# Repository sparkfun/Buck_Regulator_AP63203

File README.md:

SparkFun Buck Regulator and Baby Buck Regulator
========================================

<table class="table table-hover table-striped table-bordered">
    <tr>
        <th class="text-center"> 
        </th>
        <th class="text-center">
        </th>
    </tr>
    <tr align="center">
        <td></td>
        <td></td>
    </tr>
    <tr align="center">
        <td><a href="https://www.sparkfun.com/products/18356">SparkFun Buck Regulator Breakout - 3.3V (AP63203)</a></td>
        <td><a href="https://www.sparkfun.com/products/18357">BabyBuck Regulator Breakout - 3.3V (AP63203)</a></td>
    </tr>
</table>

Who doesn't occasionally need power regulation? We certainly do, so we've designed the SparkFun Buck Regulator and Baby Buck Regulator Breakouts to help us with just such a task. Featuring the AP63203 from Diodes Inc, these breakout boards take advantage of a 2A synchronous buck converter that has a wide input voltage range of 3.8V to 32V and fully integrated 125mΩ high-side power MOSFET/68mΩ lowside power MOSFET to provide high-efficiency step-down DC/DC conversion. All of this snuggled up in a low-profile, TSOT26 package that's integrated into either a 1in. by 1in. or 0.4x0.5" board. 

Input power for the Buck Regulator can be supplied in a number of ways. There are screw terminals on the right side of the board, solder pads for a barrel jack, which can be mounted on the top or bottom side of the board, and the plated through holes on the left side of the board can all be used as input. Output can be obtained via the screw terminals or the plated through holes. Additionally, to dissipate some of the excess heat, we've added a copper pad for a heat sink on the back of the board.

Unlike it's sibling, the BabyBuck sacrifices power option flexibility for space. Don't worry, though, because you can still use the plated through holes for input and output power. With some simple [right-angle headers](https://www.sparkfun.com/products/553), you'll be up and running in no time.

Frequency Spread Spectrum (FSS) reduces EMI and a proprietary gate driver scheme resists switching node ringing without sacrificing MOSFET turn-on and turn-off times, which further erases high-frequency radiated EMI noise.

Repository Contents
-------------------

* **/SparkFun Buck Regulator - AP63203**
    * **/Hardware** - Eagle design files (.brd, .sch)
        * **/Production** - Production panel files (.brd)
* **/SparkFun BabyBuck Regulator - AP63203**
    * **/Hardware** - Eagle design files (.brd, .sch)
        * **/Production** - Production panel files (.brd)

Documentation
--------------
* **[Hookup Guide](https://learn.sparkfun.com/tutorials/buck-regulator-hookup-guide)** - Basic hookup guide for the Buck Regulator and Baby Buck Regulator.
* **[SparkFun Fritzing repo](https://github.com/sparkfun/Fritzing_Parts)** - Fritzing diagrams for SparkFun products.

License Information
-------------------

This product is _**open source**_! 

Please review the LICENSE.md file for license information. 

If you have any questions or concerns on licensing, please contact technical support on our [SparkFun forums](https://forum.sparkfun.com/viewforum.php?f=152).

Distributed as-is; no warranty is given.

- Your friends at SparkFun.

_<COLLABORATION CREDIT>_

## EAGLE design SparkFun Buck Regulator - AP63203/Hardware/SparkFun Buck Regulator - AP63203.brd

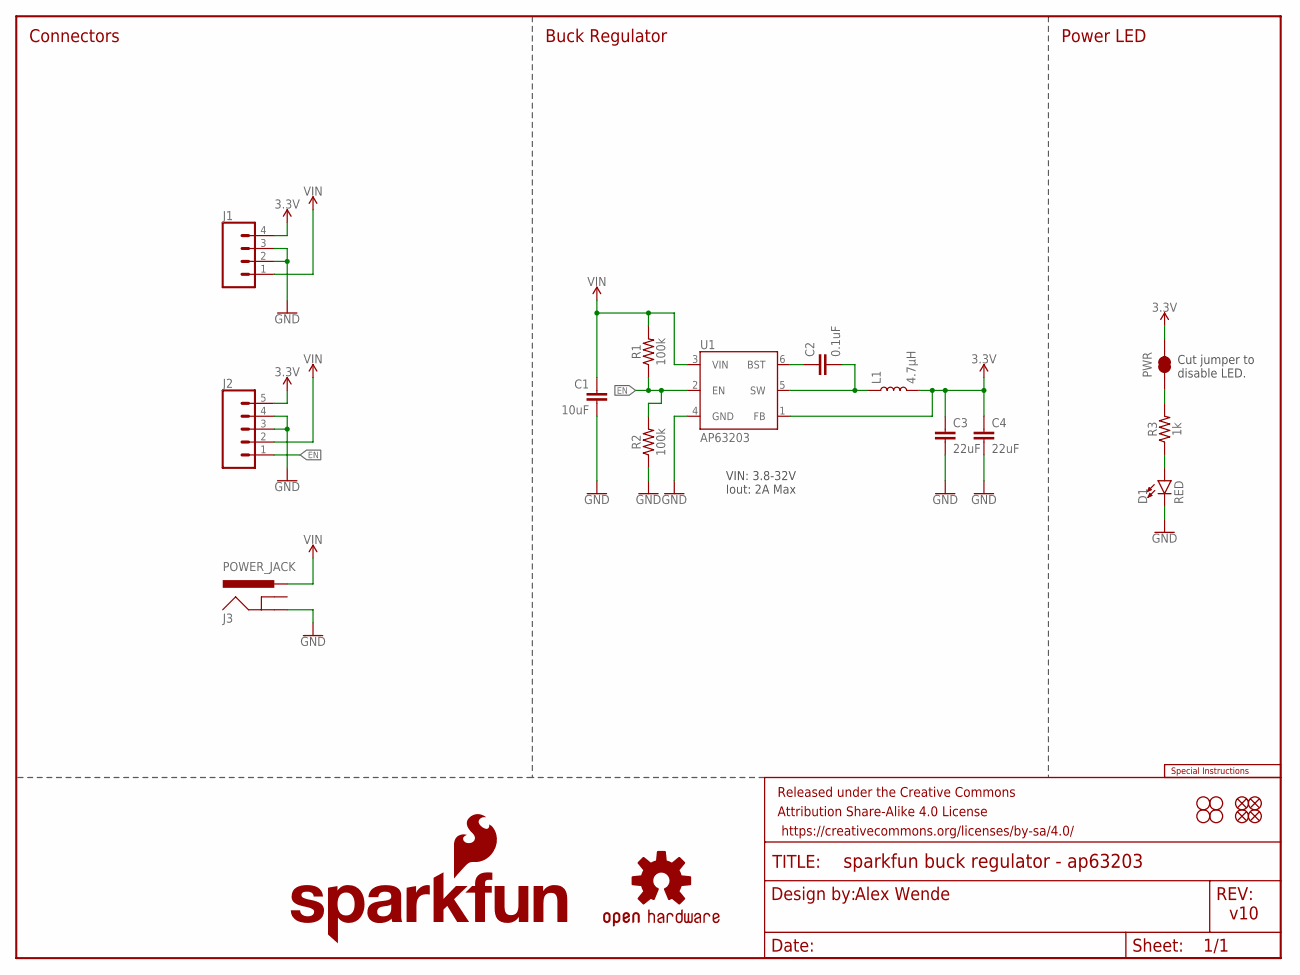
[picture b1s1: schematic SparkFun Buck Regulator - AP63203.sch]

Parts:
C1: 10uF; 1210
C2: 0.1uF; 0603
C3, C4: 22uF; 0603
D1: RED; LED-0603
FD1, FD2, FD3, FD4: FIDUCIALUFIDUCIAL; FIDUCIAL-MICRO
FRAME1: FRAME-LETTER; CREATIVE_COMMONS
H1, H2, H3, H4: STAND-OFF
J1: CONN_04SCREW; SCREWTERMINAL-3.5MM-4
J2: CONN_05NO_SILK; 1X05_NO_SILK
J3: POWER_JACK; POWER_JACK_PTH_SLOT
L1: 4.7μH; INDUCTOR_4X4MM
LOGO1: SFE_LOGO_NAME_FLAME.1_INCH; SFE_LOGO_NAME_FLAME_.1
LOGO2: OSHW-LOGOS; OSHW-LOGO-S
LOGO3: SPECIAL_INSTRUCTIONS-ORDERING; ORDERING_INSTRUCTIONS
PWR: JUMPER-SMT_2_NC_TRACE_SILK; SMT-JUMPER_2_NC_TRACE_SILK
R1, R2: 100k; 0603
R3: 1k; 0603
U1: AP63203; SOT23-6

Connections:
3.3V: C3.1, C4.1, J1.4, J2.5, L1.P$2 (2), PWR.2, U1.1 (FB)
EN: J2.1, R1.1, R2.2, U1.2 (EN)
GND: C1.2, C3.2, C4.2, D1.C, J1.2, J1.3, J2.3, J2.4, J3.GND, R2.1, U1.4 (GND)
unnamed: D1.A, R3.1
unnamed: PWR.1, R3.2
unnamed: C2.1, U1.6 (BST)
unnamed: C2.2, L1.P$1 (1), U1.5 (SW)
VIN: C1.1, J1.1, J2.2, J3.PWR, R1.2, U1.3 (VIN)

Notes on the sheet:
Alex Wende
v10
Buck Regulator
Connectors
VIN: 3.8-32V Iout: 2A Max
Power LED
Cut jumper to disable LED.

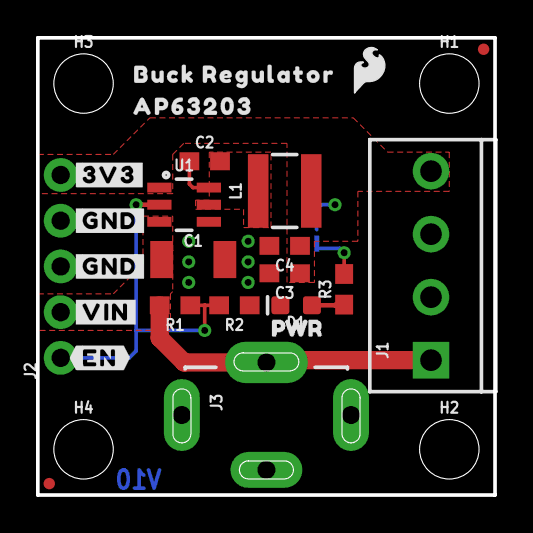
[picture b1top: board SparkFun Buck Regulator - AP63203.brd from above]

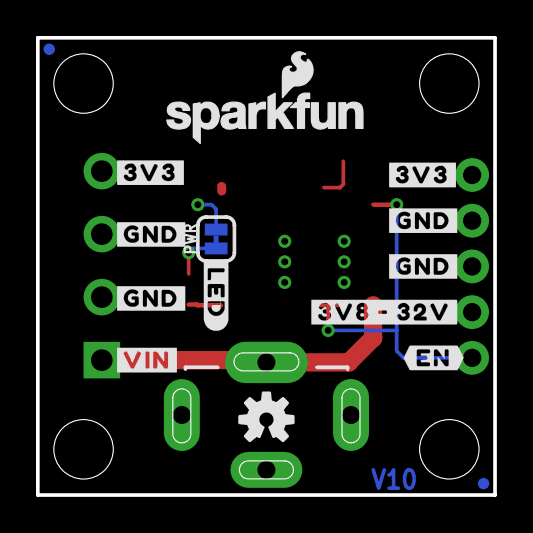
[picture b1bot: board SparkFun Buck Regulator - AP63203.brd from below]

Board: 2 copper layers, 25.4 x 25.4 mm, 45 parts (15 on the bottom side), 8 nets.

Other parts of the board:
U$1, U$2, U$13: #3V3#0
U$3, U$4, U$5, U$10, U$11, U$12: #GND#0
U$6, U$8: #VIN#0
U$7, U$14: #EN#0
U$9: #3V8_#_32V#0
U$15: BUCK_REGULATOR0
U$16: #LED#0
U$17: SFE_LOGO_FLAME_.1
U$18: PWR1
U$20: AP632030

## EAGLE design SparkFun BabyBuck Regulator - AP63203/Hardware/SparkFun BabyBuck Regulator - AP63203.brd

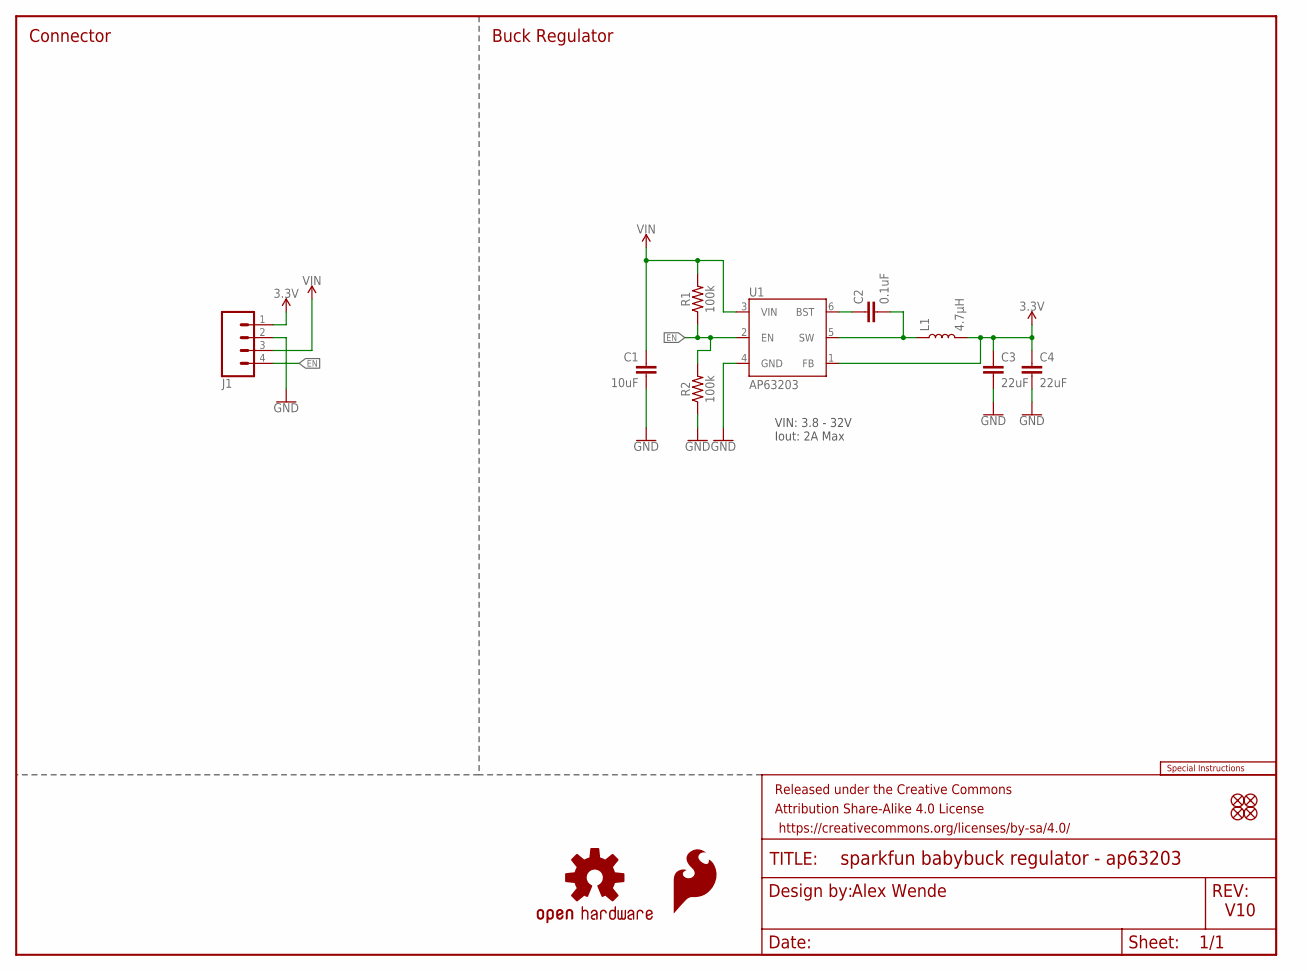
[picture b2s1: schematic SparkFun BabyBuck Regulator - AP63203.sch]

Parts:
C1: 10uF; 1210
C2: 0.1uF; 0603
C3, C4: 22uF; 0603
FD1, FD2, FD3, FD4: FIDUCIAL0.2MM; FIDUCIAL-0.2MM
FRAME1: FRAME-LETTER; CREATIVE_COMMONS
J1: CONN_041X04_NO_SILK; 1X04_NO_SILK
L1: 4.7μH; INDUCTOR_4X4MM
LOGO1: SFE_LOGO_FLAME.1_INCH; SFE_LOGO_FLAME_.1
LOGO2: OSHW-LOGOS; OSHW-LOGO-S
LOGO3: SPECIAL_INSTRUCTIONS-ORDERING; ORDERING_INSTRUCTIONS
R1, R2: 100k; 0603
U1: AP63203; SOT23-6

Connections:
3.3V: C3.1, C4.1, J1.1, L1.P$2 (2), U1.1 (FB)
EN: J1.4, R1.1, R2.2, U1.2 (EN)
GND: C1.2, C3.2, C4.2, J1.2, R2.1, U1.4 (GND)
unnamed: C2.1, U1.6 (BST)
unnamed: C2.2, L1.P$1 (1), U1.5 (SW)
VIN: C1.1, J1.3, R1.2, U1.3 (VIN)

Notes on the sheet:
Alex Wende
V10
Buck Regulator
Connector
VIN: 3.8 - 32V Iout: 2A Max

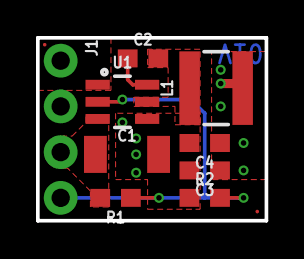
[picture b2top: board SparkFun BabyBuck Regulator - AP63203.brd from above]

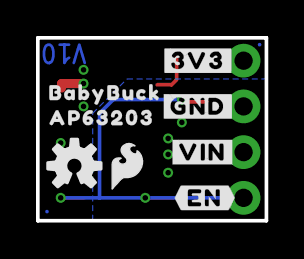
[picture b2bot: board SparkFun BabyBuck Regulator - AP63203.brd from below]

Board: 2 copper layers, 12.7 x 10.2 mm, 23 parts (10 on the bottom side), 6 nets.

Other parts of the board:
U$1: #3V3#0
U$2: #GND#0
U$3: #VIN#0
U$4: #EN#0
U$7: AP632030
U$8: BABYBUCK0

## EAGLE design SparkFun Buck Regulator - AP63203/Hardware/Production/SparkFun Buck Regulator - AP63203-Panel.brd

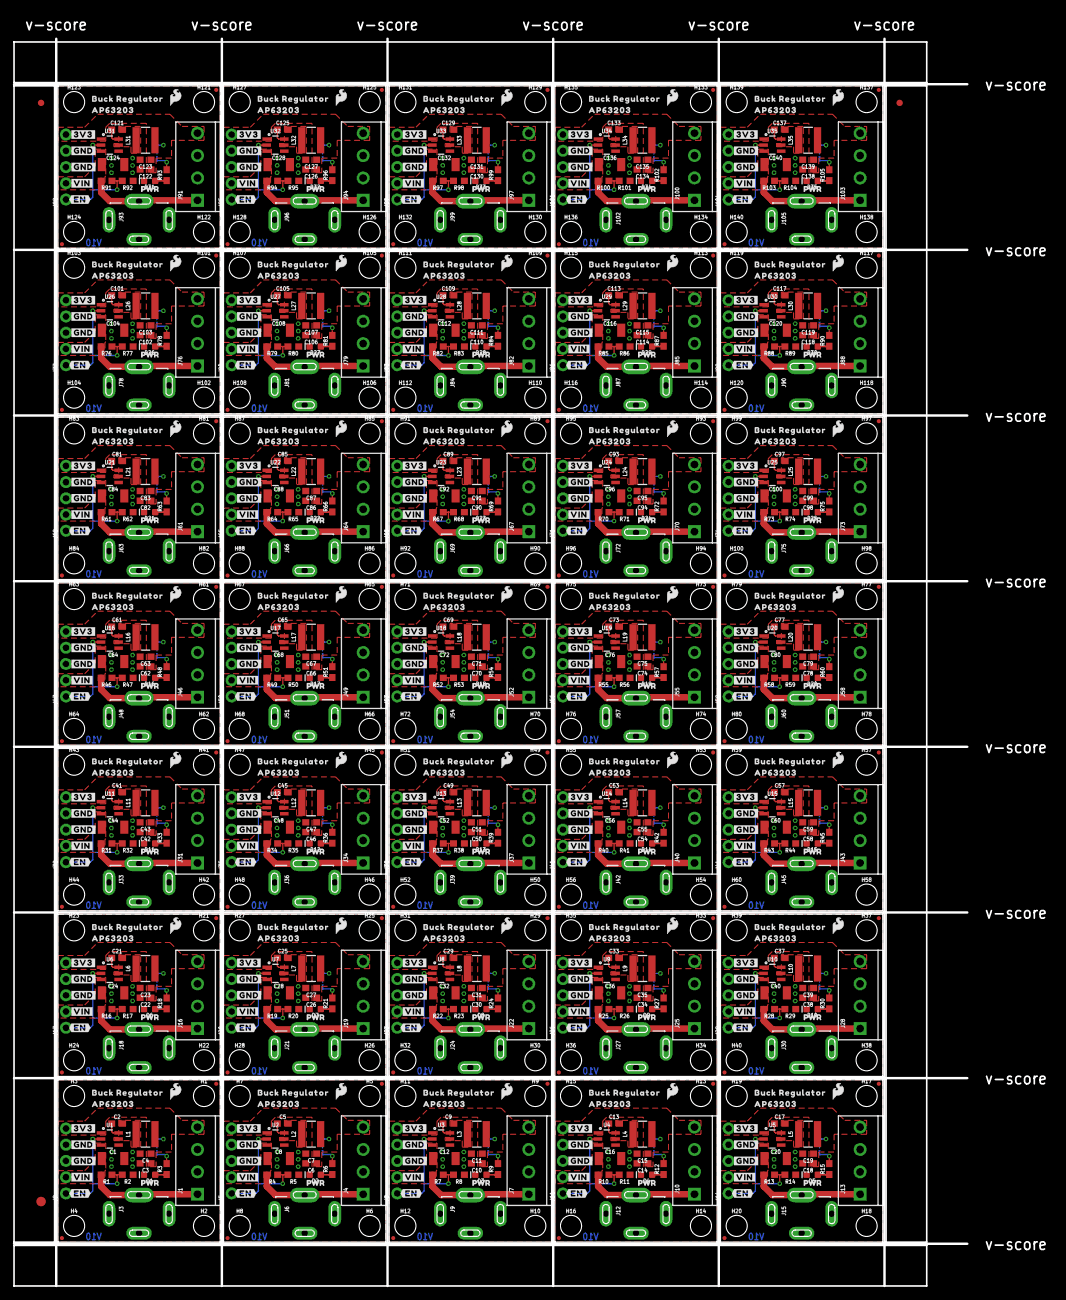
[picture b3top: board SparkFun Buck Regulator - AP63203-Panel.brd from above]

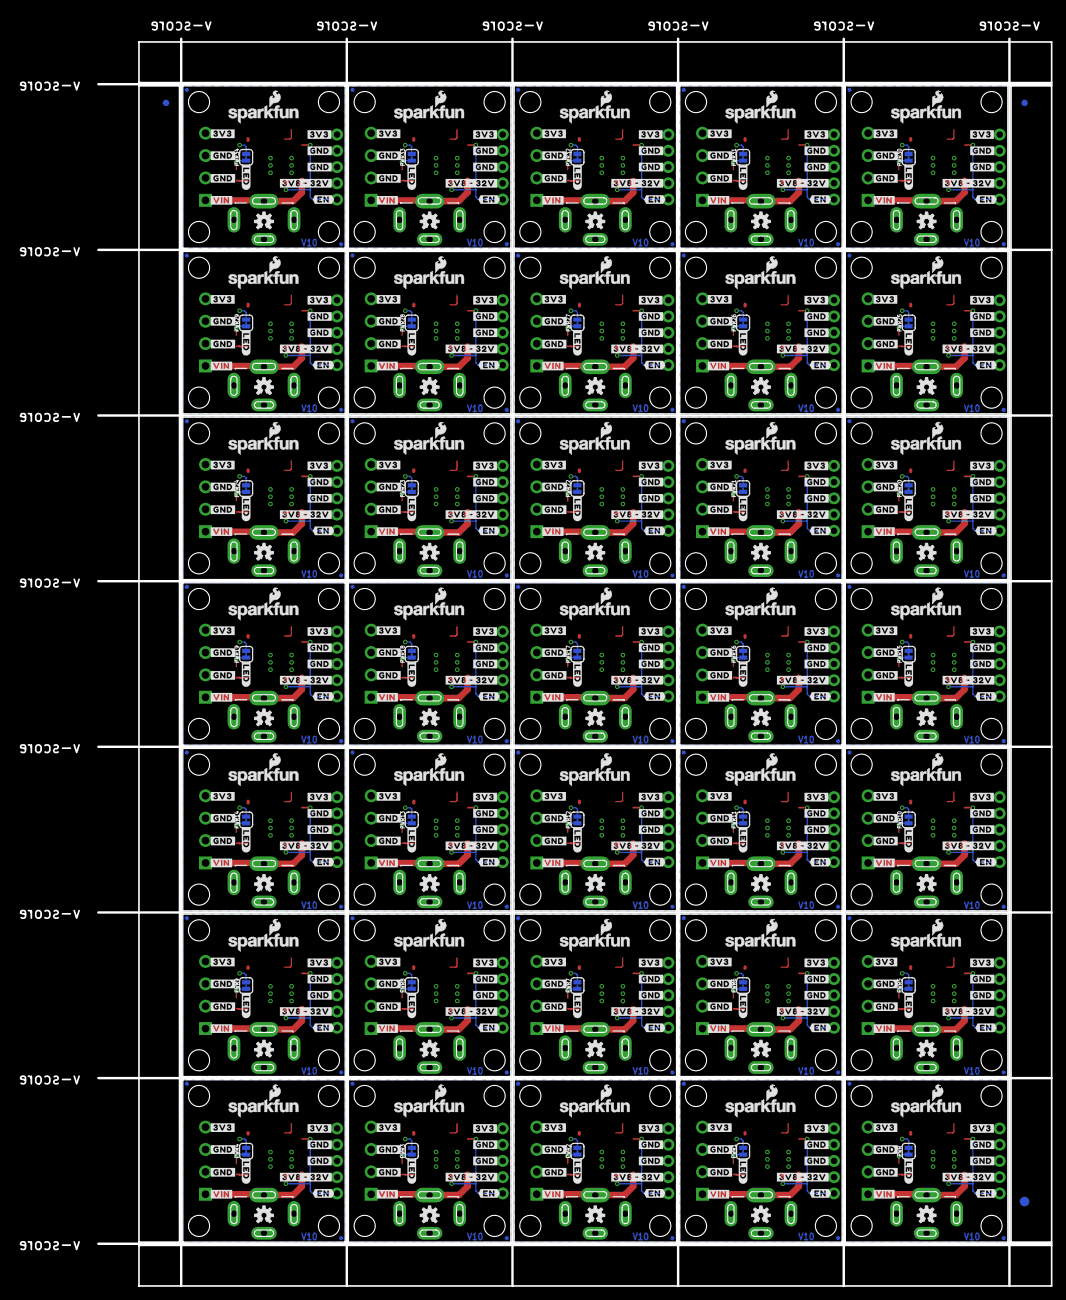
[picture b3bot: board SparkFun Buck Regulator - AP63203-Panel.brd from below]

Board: 2 copper layers, 149.1 x 195.1 mm, 1511 parts (528 on the bottom side), 280 nets.

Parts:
C1, C8, C12, C16, C20, C24, C28, C32, C36, C40, C44, C48, C52, C56, C60, C64, C68, C72, C76, C80, C84, C88, C92, C96, C100, C104, C108, C112, C116, C120, C124, C128, C132, C136, C140: 10uF; 1210
C2, C5, C9, C13, C17, C21, C25, C29, C33, C37, C41, C45, C49, C53, C57, C61, C65, C69, C73, C77, C81, C85, C89, C93, C97, C101, C105, C109, C113, C117, C121, C125, C129, C133, C137: 0.1uF; 0603
C3, C4, C6, C7, C10, C11, C14, C15, C18, C19, C22, C23, C26, C27, C30, C31, C34, C35, C38, C39, C42, C43, C46, C47, C50, C51, C54, C55, C58, C59, C62, C63, C66, C67, C70, C71, C74, C75, C78, C79, C82, C83, C86, C87, C90, C91, C94, C95, C98, C99, C102, C103, C106, C107, C110, C111, C114, C115, C118, C119, C122, C123, C126, C127, C130, C131, C134, C135, C138, C139: 22uF; 0603
D1, D2, D3, D4, D5, D6, D7, D8, D9, D10, D11, D12, D13, D14, D15, D16, D17, D18, D19, D20, D21, D22, D23, D24, D25, D26, D27, D28, D29, D30, D31, D32, D33, D34, D35: RED; LED-0603
E$1, E$2, E$3, E$4: FIDUCIAL-1X2
E$5, E$6: FIDUCIAL-1.5X3
FD1, FD2, FD3, FD4, FD5, FD6, FD7, FD8, FD9, FD10, FD11, FD12, FD13, FD14, FD15, FD16, FD17, FD18, FD19, FD20, FD21, FD22, FD23, FD24, FD25, FD26, FD27, FD28, FD29, FD30, FD31, FD32, FD33, FD34, FD35, FD36, FD37, FD38, FD39, FD40, FD41, FD42, FD43, FD44, FD45, FD46, FD47, FD48, FD49, FD50, FD51, FD52, FD53, FD54, FD55, FD56, FD57, FD58, FD59, FD60, FD61, FD62, FD63, FD64, FD65, FD66, FD67, FD68, FD69, FD70, FD71, FD72, FD73, FD74, FD75, FD76, FD77, FD78, FD79, FD80, FD81, FD82, FD83, FD84, FD85, FD86, FD87, FD88, FD89, FD90, FD91, FD92, FD93, FD94, FD95, FD96, FD97, FD98, FD99, FD100, FD101, FD102, FD103, FD104, FD105, FD106, FD107, FD108, FD109, FD110, FD111, FD112, FD113, FD114, FD115, FD116, FD117, FD118, FD119, FD120, FD121, FD122, FD123, FD124, FD125, FD126, FD127, FD128, FD129, FD130, FD131, FD132, FD133, FD134, FD135, FD136, FD137, FD138, FD139, FD140: FIDUCIALUFIDUCIAL; FIDUCIAL-MICRO
H1, H2, H3, H4, H5, H6, H7, H8, H9, H10, H11, H12, H13, H14, H15, H16, H17, H18, H19, H20, H21, H22, H23, H24, H25, H26, H27, H28, H29, H30, H31, H32, H33, H34, H35, H36, H37, H38, H39, H40, H41, H42, H43, H44, H45, H46, H47, H48, H49, H50, H51, H52, H53, H54, H55, H56, H57, H58, H59, H60, H61, H62, H63, H64, H65, H66, H67, H68, H69, H70, H71, H72, H73, H74, H75, H76, H77, H78, H79, H80, H81, H82, H83, H84, H85, H86, H87, H88, H89, H90, H91, H92, H93, H94, H95, H96, H97, H98, H99, H100, H101, H102, H103, H104, H105, H106, H107, H108, H109, H110, H111, H112, H113, H114, H115, H116, H117, H118, H119, H120, H121, H122, H123, H124, H125, H126, H127, H128, H129, H130, H131, H132, H133, H134, H135, H136, H137, H138, H139, H140: STAND-OFF
J1, J4, J7, J10, J13, J16, J19, J22, J25, J28, J31, J34, J37, J40, J43, J46, J49, J52, J55, J58, J61, J64, J67, J70, J73, J76, J79, J82, J85, J88, J91, J94, J97, J100, J103: SCREWTERMINAL-3.5MM-4
J2, J5, J8, J11, J14, J17, J20, J23, J26, J29, J32, J35, J38, J41, J44, J47, J50, J53, J56, J59, J62, J65, J68, J71, J74, J77, J80, J83, J86, J89, J92, J95, J98, J101, J104: 1X05_NO_SILK
J3, J6, J9, J12, J15, J18, J21, J24, J27, J30, J33, J36, J39, J42, J45, J48, J51, J54, J57, J60, J63, J66, J69, J72, J75, J78, J81, J84, J87, J90, J93, J96, J99, J102, J105: POWER_JACK; POWER_JACK_PTH_SLOT
L1, L2, L3, L4, L5, L6, L7, L8, L9, L10, L11, L12, L13, L14, L15, L16, L17, L18, L19, L20, L21, L22, L23, L24, L25, L26, L27, L28, L29, L30, L31, L32, L33, L34, L35: 4.7μH; INDUCTOR_4X4MM
LOGO1, LOGO3, LOGO5, LOGO7, LOGO9, LOGO11, LOGO13, LOGO15, LOGO17, LOGO19, LOGO21, LOGO23, LOGO25, LOGO27, LOGO29, LOGO31, LOGO33, LOGO35, LOGO37, LOGO39, LOGO41, LOGO43, LOGO45, LOGO47, LOGO49, LOGO51, LOGO53, LOGO55, LOGO57, LOGO59, LOGO61, LOGO63, LOGO65, LOGO67, LOGO69: SFE_LOGO_NAME_FLAME.1_INCH; SFE_LOGO_NAME_FLAME_.1
LOGO2, LOGO4, LOGO6, LOGO8, LOGO10, LOGO12, LOGO14, LOGO16, LOGO18, LOGO20, LOGO22, LOGO24, LOGO26, LOGO28, LOGO30, LOGO32, LOGO34, LOGO36, LOGO38, LOGO40, LOGO42, LOGO44, LOGO46, LOGO48, LOGO50, LOGO52, LOGO54, LOGO56, LOGO58, LOGO60, LOGO62, LOGO64, LOGO66, LOGO68, LOGO70: OSHW-LOGOS; OSHW-LOGO-S
PWR, PWR1, PWR2, PWR3, PWR4, PWR5, PWR6, PWR7, PWR8, PWR9, PWR10, PWR11, PWR12, PWR13, PWR14, PWR15, PWR16, PWR17, PWR18, PWR19, PWR20, PWR21, PWR22, PWR23, PWR24, PWR25, PWR26, PWR27, PWR28, PWR29, PWR30, PWR31, PWR32, PWR33, PWR34: SMT-JUMPER_2_NC_TRACE_SILK
R1, R2, R4, R5, R7, R8, R10, R11, R13, R14, R16, R17, R19, R20, R22, R23, R25, R26, R28, R29, R31, R32, R34, R35, R37, R38, R40, R41, R43, R44, R46, R47, R49, R50, R52, R53, R55, R56, R58, R59, R61, R62, R64, R65, R67, R68, R70, R71, R73, R74, R76, R77, R79, R80, R82, R83, R85, R86, R88, R89, R91, R92, R94, R95, R97, R98, R100, R101, R103, R104: 100k; 0603
R3, R6, R9, R12, R15, R18, R21, R24, R27, R30, R33, R36, R39, R42, R45, R48, R51, R54, R57, R60, R63, R66, R69, R72, R75, R78, R81, R84, R87, R90, R93, R96, R99, R102, R105: 1k; 0603
U1, U2, U3, U4, U5, U6, U7, U8, U9, U10, U11, U12, U13, U14, U15, U16, U17, U18, U19, U20, U21, U22, U23, U24, U25, U26, U27, U28, U29, U30, U31, U32, U33, U34, U35: AP63203; SOT23-6
U$1, U$2, U$13, U$19, U$21, U$31, U$39, U$40, U$50, U$58, U$59, U$69, U$77, U$78, U$88, U$96, U$97, U$107, U$115, U$116, U$126, U$134, U$135, U$145, U$153, U$154, U$164, U$172, U$173, U$183, U$191, U$192, U$202, U$210, U$211, U$221, U$229, U$230, U$240, U$248, U$249, U$259, U$267, U$268, U$278, U$286, U$287, U$297, U$305, U$306, U$316, U$324, U$325, U$335, U$343, U$344, U$354, U$362, U$363, U$373, U$381, U$382, U$392, U$400, U$401, U$411, U$419, U$420, U$430, U$438, U$439, U$449, U$457, U$458, U$468, U$476, U$477, U$487, U$495, U$496, U$506, U$514, U$515, U$525, U$533, U$534, U$544, U$552, U$553, U$563, U$571, U$572, U$582, U$590, U$591, U$601, U$609, U$610, U$620, U$628, U$629, U$639, U$647, U$648, U$658: #3V3#0
U$3, U$4, U$5, U$10, U$11, U$12, U$22, U$23, U$24, U$28, U$29, U$30, U$41, U$42, U$43, U$47, U$48, U$49, U$60, U$61, U$62, U$66, U$67, U$68, U$79, U$80, U$81, U$85, U$86, U$87, U$98, U$99, U$100, U$104, U$105, U$106, U$117, U$118, U$119, U$123, U$124, U$125, U$136, U$137, U$138, U$142, U$143, U$144, U$155, U$156, U$157, U$161, U$162, U$163, U$174, U$175, U$176, U$180, U$181, U$182, U$193, U$194, U$195, U$199, U$200, U$201, U$212, U$213, U$214, U$218, U$219, U$220, U$231, U$232, U$233, U$237, U$238, U$239, U$250, U$251, U$252, U$256, U$257, U$258, U$269, U$270, U$271, U$275, U$276, U$277, U$288, U$289, U$290, U$294, U$295, U$296, U$307, U$308, U$309, U$313, U$314, U$315, U$326, U$327, U$328, U$332, U$333, U$334, U$345, U$346, U$347, U$351, U$352, U$353, U$364, U$365, U$366, U$370, U$371, U$372, U$383, U$384, U$385, U$389, U$390, U$391, U$402, U$403, U$404, U$408, U$409, U$410, U$421, U$422, U$423, U$427, U$428, U$429, U$440, U$441, U$442, U$446, U$447, U$448, U$459, U$460, U$461, U$465, U$466, U$467, U$478, U$479, U$480, U$484, U$485, U$486, U$497, U$498, U$499, U$503, U$504, U$505, U$516, U$517, U$518, U$522, U$523, U$524, U$535, U$536, U$537, U$541, U$542, U$543, U$554, U$555, U$556, U$560, U$561, U$562, U$573, U$574, U$575, U$579, U$580, U$581, U$592, U$593, U$594, U$598, U$599, U$600, U$611, U$612, U$613, U$617, U$618, U$619, U$630, U$631, U$632, U$636, U$637, U$638, U$649, U$650, U$651, U$655, U$656, U$657: #GND#0
U$6, U$8, U$25, U$34, U$44, U$53, U$63, U$72, U$82, U$91, U$101, U$110, U$120, U$129, U$139, U$148, U$158, U$167, U$177, U$186, U$196, U$205, U$215, U$224, U$234, U$243, U$253, U$262, U$272, U$281, U$291, U$300, U$310, U$319, U$329, U$338, U$348, U$357, U$367, U$376, U$386, U$395, U$405, U$414, U$424, U$433, U$443, U$452, U$462, U$471, U$481, U$490, U$500, U$509, U$519, U$528, U$538, U$547, U$557, U$566, U$576, U$585, U$595, U$604, U$614, U$623, U$633, U$642, U$652, U$661: #VIN#0
U$7, U$14, U$26, U$32, U$45, U$51, U$64, U$70, U$83, U$89, U$102, U$108, U$121, U$127, U$140, U$146, U$159, U$165, U$178, U$184, U$197, U$203, U$216, U$222, U$235, U$241, U$254, U$260, U$273, U$279, U$292, U$298, U$311, U$317, U$330, U$336, U$349, U$355, U$368, U$374, U$387, U$393, U$406, U$412, U$425, U$431, U$444, U$450, U$463, U$469, U$482, U$488, U$501, U$507, U$520, U$526, U$539, U$545, U$558, U$564, U$577, U$583, U$596, U$602, U$615, U$621, U$634, U$640, U$653, U$659: #EN#0
U$9, U$27, U$46, U$65, U$84, U$103, U$122, U$141, U$160, U$179, U$198, U$217, U$236, U$255, U$274, U$293, U$312, U$331, U$350, U$369, U$388, U$407, U$426, U$445, U$464, U$483, U$502, U$521, U$540, U$559, U$578, U$597, U$616, U$635, U$654: #3V8_#_32V#0
U$15, U$33, U$52, U$71, U$90, U$109, U$128, U$147, U$166, U$185, U$204, U$223, U$242, U$261, U$280, U$299, U$318, U$337, U$356, U$375, U$394, U$413, U$432, U$451, U$470, U$489, U$508, U$527, U$546, U$565, U$584, U$603, U$622, U$641, U$660: BUCK_REGULATOR0
U$16, U$38, U$57, U$76, U$95, U$114, U$133, U$152, U$171, U$190, U$209, U$228, U$247, U$266, U$285, U$304, U$323, U$342, U$361, U$380, U$399, U$418, U$437, U$456, U$475, U$494, U$513, U$532, U$551, U$570, U$589, U$608, U$627, U$646, U$665: #LED#0
U$17, U$35, U$54, U$73, U$92, U$111, U$130, U$149, U$168, U$187, U$206, U$225, U$244, U$263, U$282, U$301, U$320, U$339, U$358, U$377, U$396, U$415, U$434, U$453, U$472, U$491, U$510, U$529, U$548, U$567, U$586, U$605, U$624, U$643, U$662: SFE_LOGO_FLAME_.1
U$18, U$36, U$55, U$74, U$93, U$112, U$131, U$150, U$169, U$188, U$207, U$226, U$245, U$264, U$283, U$302, U$321, U$340, U$359, U$378, U$397, U$416, U$435, U$454, U$473, U$492, U$511, U$530, U$549, U$568, U$587, U$606, U$625, U$644, U$663: PWR1
U$20, U$37, U$56, U$75, U$94, U$113, U$132, U$151, U$170, U$189, U$208, U$227, U$246, U$265, U$284, U$303, U$322, U$341, U$360, U$379, U$398, U$417, U$436, U$455, U$474, U$493, U$512, U$531, U$550, U$569, U$588, U$607, U$626, U$645, U$664: AP632030

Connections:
3.3V: C3.1, C4.1, J1.4, J2.5, L1.P$2, PWR.2, U1.1
3.3V1: C6.1, C7.1, J4.4, J5.5, L2.P$2, PWR1.2, U2.1
3.3V2: C10.1, C11.1, J7.4, J8.5, L3.P$2, PWR2.2, U3.1
3.3V3: C14.1, C15.1, J10.4, J11.5, L4.P$2, PWR3.2, U4.1
3.3V4: C18.1, C19.1, J13.4, J14.5, L5.P$2, PWR4.2, U5.1
3.3V5: C22.1, C23.1, J16.4, J17.5, L6.P$2, PWR5.2, U6.1
3.3V6: C26.1, C27.1, J19.4, J20.5, L7.P$2, PWR6.2, U7.1
3.3V7: C30.1, C31.1, J22.4, J23.5, L8.P$2, PWR7.2, U8.1
3.3V8: C34.1, C35.1, J25.4, J26.5, L9.P$2, PWR8.2, U9.1
3.3V9: C38.1, C39.1, J28.4, J29.5, L10.P$2, PWR9.2, U10.1
3.3V10: C42.1, C43.1, J31.4, J32.5, L11.P$2, PWR10.2, U11.1
3.3V11: C46.1, C47.1, J34.4, J35.5, L12.P$2, PWR11.2, U12.1
3.3V12: C50.1, C51.1, J37.4, J38.5, L13.P$2, PWR12.2, U13.1
3.3V13: C54.1, C55.1, J40.4, J41.5, L14.P$2, PWR13.2, U14.1
3.3V14: C58.1, C59.1, J43.4, J44.5, L15.P$2, PWR14.2, U15.1
3.3V15: C62.1, C63.1, J46.4, J47.5, L16.P$2, PWR15.2, U16.1
3.3V16: C66.1, C67.1, J49.4, J50.5, L17.P$2, PWR16.2, U17.1
3.3V17: C70.1, C71.1, J52.4, J53.5, L18.P$2, PWR17.2, U18.1
3.3V18: C74.1, C75.1, J55.4, J56.5, L19.P$2, PWR18.2, U19.1
3.3V19: C78.1, C79.1, J58.4, J59.5, L20.P$2, PWR19.2, U20.1
3.3V20: C82.1, C83.1, J61.4, J62.5, L21.P$2, PWR20.2, U21.1
3.3V21: C86.1, C87.1, J64.4, J65.5, L22.P$2, PWR21.2, U22.1
3.3V22: C90.1, C91.1, J67.4, J68.5, L23.P$2, PWR22.2, U23.1
3.3V23: C94.1, C95.1, J70.4, J71.5, L24.P$2, PWR23.2, U24.1
3.3V24: C98.1, C99.1, J73.4, J74.5, L25.P$2, PWR24.2, U25.1
3.3V25: C102.1, C103.1, J76.4, J77.5, L26.P$2, PWR25.2, U26.1
3.3V26: C106.1, C107.1, J79.4, J80.5, L27.P$2, PWR26.2, U27.1
3.3V27: C110.1, C111.1, J82.4, J83.5, L28.P$2, PWR27.2, U28.1
3.3V28: C114.1, C115.1, J85.4, J86.5, L29.P$2, PWR28.2, U29.1
3.3V29: C118.1, C119.1, J88.4, J89.5, L30.P$2, PWR29.2, U30.1
3.3V30: C122.1, C123.1, J91.4, J92.5, L31.P$2, PWR30.2, U31.1
3.3V31: C126.1, C127.1, J94.4, J95.5, L32.P$2, PWR31.2, U32.1
3.3V32: C130.1, C131.1, J97.4, J98.5, L33.P$2, PWR32.2, U33.1
3.3V33: C134.1, C135.1, J100.4, J101.5, L34.P$2, PWR33.2, U34.1
3.3V34: C138.1, C139.1, J103.4, J104.5, L35.P$2, PWR34.2, U35.1
EN: J2.1, R1.1, R2.2, U1.2
EN1: J5.1, R4.1, R5.2, U2.2
EN2: J8.1, R7.1, R8.2, U3.2
EN3: J11.1, R10.1, R11.2, U4.2
EN4: J14.1, R13.1, R14.2, U5.2
EN5: J17.1, R16.1, R17.2, U6.2
EN6: J20.1, R19.1, R20.2, U7.2
EN7: J23.1, R22.1, R23.2, U8.2
EN8: J26.1, R25.1, R26.2, U9.2
EN9: J29.1, R28.1, R29.2, U10.2
EN10: J32.1, R31.1, R32.2, U11.2
EN11: J35.1, R34.1, R35.2, U12.2
EN12: J38.1, R37.1, R38.2, U13.2
EN13: J41.1, R40.1, R41.2, U14.2
EN14: J44.1, R43.1, R44.2, U15.2
EN15: J47.1, R46.1, R47.2, U16.2
EN16: J50.1, R49.1, R50.2, U17.2
EN17: J53.1, R52.1, R53.2, U18.2
EN18: J56.1, R55.1, R56.2, U19.2
EN19: J59.1, R58.1, R59.2, U20.2
EN20: J62.1, R61.1, R62.2, U21.2
EN21: J65.1, R64.1, R65.2, U22.2
EN22: J68.1, R67.1, R68.2, U23.2
EN23: J71.1, R70.1, R71.2, U24.2
EN24: J74.1, R73.1, R74.2, U25.2
EN25: J77.1, R76.1, R77.2, U26.2
EN26: J80.1, R79.1, R80.2, U27.2
EN27: J83.1, R82.1, R83.2, U28.2
EN28: J86.1, R85.1, R86.2, U29.2
EN29: J89.1, R88.1, R89.2, U30.2
EN30: J92.1, R91.1, R92.2, U31.2
EN31: J95.1, R94.1, R95.2, U32.2
EN32: J98.1, R97.1, R98.2, U33.2
EN33: J101.1, R100.1, R101.2, U34.2
EN34: J104.1, R103.1, R104.2, U35.2
GND: C1.2, C3.2, C4.2, D1.C, J1.2, J1.3, J2.3, J2.4, J3.GND, R2.1, U1.4
GND1: C6.2, C7.2, C8.2, D2.C, J4.2, J4.3, J5.3, J5.4, J6.GND, R5.1, U2.4
GND2: C10.2, C11.2, C12.2, D3.C, J7.2, J7.3, J8.3, J8.4, J9.GND, R8.1, U3.4
GND3: C14.2, C15.2, C16.2, D4.C, J10.2, J10.3, J11.3, J11.4, J12.GND, R11.1, U4.4
GND4: C18.2, C19.2, C20.2, D5.C, J13.2, J13.3, J14.3, J14.4, J15.GND, R14.1, U5.4
GND5: C22.2, C23.2, C24.2, D6.C, J16.2, J16.3, J17.3, J17.4, J18.GND, R17.1, U6.4
GND6: C26.2, C27.2, C28.2, D7.C, J19.2, J19.3, J20.3, J20.4, J21.GND, R20.1, U7.4
GND7: C30.2, C31.2, C32.2, D8.C, J22.2, J22.3, J23.3, J23.4, J24.GND, R23.1, U8.4
GND8: C34.2, C35.2, C36.2, D9.C, J25.2, J25.3, J26.3, J26.4, J27.GND, R26.1, U9.4
GND9: C38.2, C39.2, C40.2, D10.C, J28.2, J28.3, J29.3, J29.4, J30.GND, R29.1, U10.4
GND10: C42.2, C43.2, C44.2, D11.C, J31.2, J31.3, J32.3, J32.4, J33.GND, R32.1, U11.4
GND11: C46.2, C47.2, C48.2, D12.C, J34.2, J34.3, J35.3, J35.4, J36.GND, R35.1, U12.4
GND12: C50.2, C51.2, C52.2, D13.C, J37.2, J37.3, J38.3, J38.4, J39.GND, R38.1, U13.4
GND13: C54.2, C55.2, C56.2, D14.C, J40.2, J40.3, J41.3, J41.4, J42.GND, R41.1, U14.4
GND14: C58.2, C59.2, C60.2, D15.C, J43.2, J43.3, J44.3, J44.4, J45.GND, R44.1, U15.4
GND15: C62.2, C63.2, C64.2, D16.C, J46.2, J46.3, J47.3, J47.4, J48.GND, R47.1, U16.4
GND16: C66.2, C67.2, C68.2, D17.C, J49.2, J49.3, J50.3, J50.4, J51.GND, R50.1, U17.4
GND17: C70.2, C71.2, C72.2, D18.C, J52.2, J52.3, J53.3, J53.4, J54.GND, R53.1, U18.4
GND18: C74.2, C75.2, C76.2, D19.C, J55.2, J55.3, J56.3, J56.4, J57.GND, R56.1, U19.4
GND19: C78.2, C79.2, C80.2, D20.C, J58.2, J58.3, J59.3, J59.4, J60.GND, R59.1, U20.4
GND20: C82.2, C83.2, C84.2, D21.C, J61.2, J61.3, J62.3, J62.4, J63.GND, R62.1, U21.4
GND21: C86.2, C87.2, C88.2, D22.C, J64.2, J64.3, J65.3, J65.4, J66.GND, R65.1, U22.4
GND22: C90.2, C91.2, C92.2, D23.C, J67.2, J67.3, J68.3, J68.4, J69.GND, R68.1, U23.4
GND23: C94.2, C95.2, C96.2, D24.C, J70.2, J70.3, J71.3, J71.4, J72.GND, R71.1, U24.4
GND24: C98.2, C99.2, C100.2, D25.C, J73.2, J73.3, J74.3, J74.4, J75.GND, R74.1, U25.4
GND25: C102.2, C103.2, C104.2, D26.C, J76.2, J76.3, J77.3, J77.4, J78.GND, R77.1, U26.4
GND26: C106.2, C107.2, C108.2, D27.C, J79.2, J79.3, J80.3, J80.4, J81.GND, R80.1, U27.4
GND27: C110.2, C111.2, C112.2, D28.C, J82.2, J82.3, J83.3, J83.4, J84.GND, R83.1, U28.4
GND28: C114.2, C115.2, C116.2, D29.C, J85.2, J85.3, J86.3, J86.4, J87.GND, R86.1, U29.4
GND29: C118.2, C119.2, C120.2, D30.C, J88.2, J88.3, J89.3, J89.4, J90.GND, R89.1, U30.4
GND30: C122.2, C123.2, C124.2, D31.C, J91.2, J91.3, J92.3, J92.4, J93.GND, R92.1, U31.4
GND31: C126.2, C127.2, C128.2, D32.C, J94.2, J94.3, J95.3, J95.4, J96.GND, R95.1, U32.4
GND32: C130.2, C131.2, C132.2, D33.C, J97.2, J97.3, J98.3, J98.4, J99.GND, R98.1, U33.4
GND33: C134.2, C135.2, C136.2, D34.C, J100.2, J100.3, J101.3, J101.4, J102.GND, R101.1, U34.4
GND34: C138.2, C139.2, C140.2, D35.C, J103.2, J103.3, J104.3, J104.4, J105.GND, R104.1, U35.4
unnamed: D1.A, R3.1
unnamed: PWR.1, R3.2
unnamed: C5.1, U2.6
unnamed: C2.1, U1.6
unnamed: C2.2, L1.P$1, U1.5
unnamed: C5.2, L2.P$1, U2.5
unnamed: D2.A, R6.1
unnamed: PWR1.1, R6.2
unnamed: C9.1, U3.6
unnamed: C9.2, L3.P$1, U3.5
unnamed: D3.A, R9.1
unnamed: PWR2.1, R9.2
unnamed: C13.1, U4.6
unnamed: C13.2, L4.P$1, U4.5
unnamed: D4.A, R12.1
unnamed: PWR3.1, R12.2
unnamed: C17.1, U5.6
unnamed: C17.2, L5.P$1, U5.5
unnamed: D5.A, R15.1
unnamed: PWR4.1, R15.2
unnamed: C21.1, U6.6
unnamed: C21.2, L6.P$1, U6.5
unnamed: D6.A, R18.1
unnamed: PWR5.1, R18.2
unnamed: C25.1, U7.6
unnamed: C25.2, L7.P$1, U7.5
unnamed: D7.A, R21.1
unnamed: PWR6.1, R21.2
unnamed: C29.1, U8.6
unnamed: C29.2, L8.P$1, U8.5
unnamed: D8.A, R24.1
unnamed: PWR7.1, R24.2
unnamed: C33.1, U9.6
unnamed: C33.2, L9.P$1, U9.5
unnamed: D9.A, R27.1
unnamed: PWR8.1, R27.2
unnamed: C37.1, U10.6
unnamed: C37.2, L10.P$1, U10.5
unnamed: D10.A, R30.1
unnamed: PWR9.1, R30.2
unnamed: C41.1, U11.6
unnamed: C41.2, L11.P$1, U11.5
unnamed: D11.A, R33.1
unnamed: PWR10.1, R33.2
unnamed: C45.1, U12.6
unnamed: C45.2, L12.P$1, U12.5
unnamed: D12.A, R36.1
unnamed: PWR11.1, R36.2
unnamed: C49.1, U13.6
unnamed: C49.2, L13.P$1, U13.5
unnamed: D13.A, R39.1
unnamed: PWR12.1, R39.2
unnamed: C53.1, U14.6
unnamed: C53.2, L14.P$1, U14.5
unnamed: D14.A, R42.1
unnamed: PWR13.1, R42.2
unnamed: C57.1, U15.6
unnamed: C57.2, L15.P$1, U15.5
unnamed: D15.A, R45.1
unnamed: PWR14.1, R45.2
unnamed: C61.1, U16.6
unnamed: C61.2, L16.P$1, U16.5
unnamed: D16.A, R48.1
unnamed: PWR15.1, R48.2
unnamed: C65.1, U17.6
unnamed: C65.2, L17.P$1, U17.5
unnamed: D17.A, R51.1
unnamed: PWR16.1, R51.2
unnamed: C69.1, U18.6
unnamed: C69.2, L18.P$1, U18.5
unnamed: D18.A, R54.1
unnamed: PWR17.1, R54.2
unnamed: C73.1, U19.6
unnamed: C73.2, L19.P$1, U19.5
unnamed: D19.A, R57.1
unnamed: PWR18.1, R57.2
unnamed: C77.1, U20.6
unnamed: C77.2, L20.P$1, U20.5
unnamed: D20.A, R60.1
unnamed: PWR19.1, R60.2
unnamed: C81.1, U21.6
unnamed: C81.2, L21.P$1, U21.5
unnamed: D21.A, R63.1
unnamed: PWR20.1, R63.2
unnamed: C85.1, U22.6
unnamed: C85.2, L22.P$1, U22.5
unnamed: D22.A, R66.1
unnamed: PWR21.1, R66.2
unnamed: C89.1, U23.6
unnamed: C89.2, L23.P$1, U23.5
unnamed: D23.A, R69.1
unnamed: PWR22.1, R69.2
unnamed: C93.1, U24.6
unnamed: C93.2, L24.P$1, U24.5
unnamed: D24.A, R72.1
unnamed: PWR23.1, R72.2
unnamed: C97.1, U25.6
unnamed: C97.2, L25.P$1, U25.5
unnamed: D25.A, R75.1
unnamed: PWR24.1, R75.2
unnamed: C101.1, U26.6
unnamed: C101.2, L26.P$1, U26.5
unnamed: D26.A, R78.1
unnamed: PWR25.1, R78.2
unnamed: C105.1, U27.6
unnamed: C105.2, L27.P$1, U27.5
unnamed: D27.A, R81.1
unnamed: PWR26.1, R81.2
unnamed: C109.1, U28.6
unnamed: C109.2, L28.P$1, U28.5
unnamed: D28.A, R84.1
unnamed: PWR27.1, R84.2
unnamed: C113.1, U29.6
unnamed: C113.2, L29.P$1, U29.5
unnamed: D29.A, R87.1
unnamed: PWR28.1, R87.2
unnamed: C117.1, U30.6
unnamed: C117.2, L30.P$1, U30.5
unnamed: D30.A, R90.1
unnamed: PWR29.1, R90.2
unnamed: C121.1, U31.6
unnamed: C121.2, L31.P$1, U31.5
unnamed: D31.A, R93.1
unnamed: PWR30.1, R93.2
unnamed: C125.1, U32.6
unnamed: C125.2, L32.P$1, U32.5
unnamed: D32.A, R96.1
unnamed: PWR31.1, R96.2
unnamed: C129.1, U33.6
unnamed: C129.2, L33.P$1, U33.5
unnamed: D33.A, R99.1
unnamed: PWR32.1, R99.2
unnamed: C133.1, U34.6
unnamed: C133.2, L34.P$1, U34.5
unnamed: D34.A, R102.1
unnamed: PWR33.1, R102.2
unnamed: C137.1, U35.6
unnamed: C137.2, L35.P$1, U35.5
unnamed: D35.A, R105.1
unnamed: PWR34.1, R105.2
VIN: C1.1, J1.1, J2.2, J3.PWR, R1.2, U1.3
VIN1: C8.1, J4.1, J5.2, J6.PWR, R4.2, U2.3
VIN2: C12.1, J7.1, J8.2, J9.PWR, R7.2, U3.3
VIN3: C16.1, J10.1, J11.2, J12.PWR, R10.2, U4.3
VIN4: C20.1, J13.1, J14.2, J15.PWR, R13.2, U5.3
VIN5: C24.1, J16.1, J17.2, J18.PWR, R16.2, U6.3
VIN6: C28.1, J19.1, J20.2, J21.PWR, R19.2, U7.3
VIN7: C32.1, J22.1, J23.2, J24.PWR, R22.2, U8.3
VIN8: C36.1, J25.1, J26.2, J27.PWR, R25.2, U9.3
VIN9: C40.1, J28.1, J29.2, J30.PWR, R28.2, U10.3
VIN10: C44.1, J31.1, J32.2, J33.PWR, R31.2, U11.3
VIN11: C48.1, J34.1, J35.2, J36.PWR, R34.2, U12.3
VIN12: C52.1, J37.1, J38.2, J39.PWR, R37.2, U13.3
VIN13: C56.1, J40.1, J41.2, J42.PWR, R40.2, U14.3
VIN14: C60.1, J43.1, J44.2, J45.PWR, R43.2, U15.3
VIN15: C64.1, J46.1, J47.2, J48.PWR, R46.2, U16.3
VIN16: C68.1, J49.1, J50.2, J51.PWR, R49.2, U17.3
VIN17: C72.1, J52.1, J53.2, J54.PWR, R52.2, U18.3
VIN18: C76.1, J55.1, J56.2, J57.PWR, R55.2, U19.3
VIN19: C80.1, J58.1, J59.2, J60.PWR, R58.2, U20.3
VIN20: C84.1, J61.1, J62.2, J63.PWR, R61.2, U21.3
VIN21: C88.1, J64.1, J65.2, J66.PWR, R64.2, U22.3
VIN22: C92.1, J67.1, J68.2, J69.PWR, R67.2, U23.3
VIN23: C96.1, J70.1, J71.2, J72.PWR, R70.2, U24.3
VIN24: C100.1, J73.1, J74.2, J75.PWR, R73.2, U25.3
VIN25: C104.1, J76.1, J77.2, J78.PWR, R76.2, U26.3
VIN26: C108.1, J79.1, J80.2, J81.PWR, R79.2, U27.3
VIN27: C112.1, J82.1, J83.2, J84.PWR, R82.2, U28.3
VIN28: C116.1, J85.1, J86.2, J87.PWR, R85.2, U29.3
VIN29: C120.1, J88.1, J89.2, J90.PWR, R88.2, U30.3
VIN30: C124.1, J91.1, J92.2, J93.PWR, R91.2, U31.3
VIN31: C128.1, J94.1, J95.2, J96.PWR, R94.2, U32.3
VIN32: C132.1, J97.1, J98.2, J99.PWR, R97.2, U33.3
VIN33: C136.1, J100.1, J101.2, J102.PWR, R100.2, U34.3
VIN34: C140.1, J103.1, J104.2, J105.PWR, R103.2, U35.3

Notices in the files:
parts and their libraries:
SparkFun-Capacitors: Licensing: Creative Commons ShareAlike 4.0 International - https://creativecommons.org/licenses/by-sa/4.0
SparkFun-Aesthetics: Released under the Creative Commons Attribution Share-Alike 4.0 License
SparkFun-Aesthetics: https://creativecommons.org/licenses/by-sa/4.0
